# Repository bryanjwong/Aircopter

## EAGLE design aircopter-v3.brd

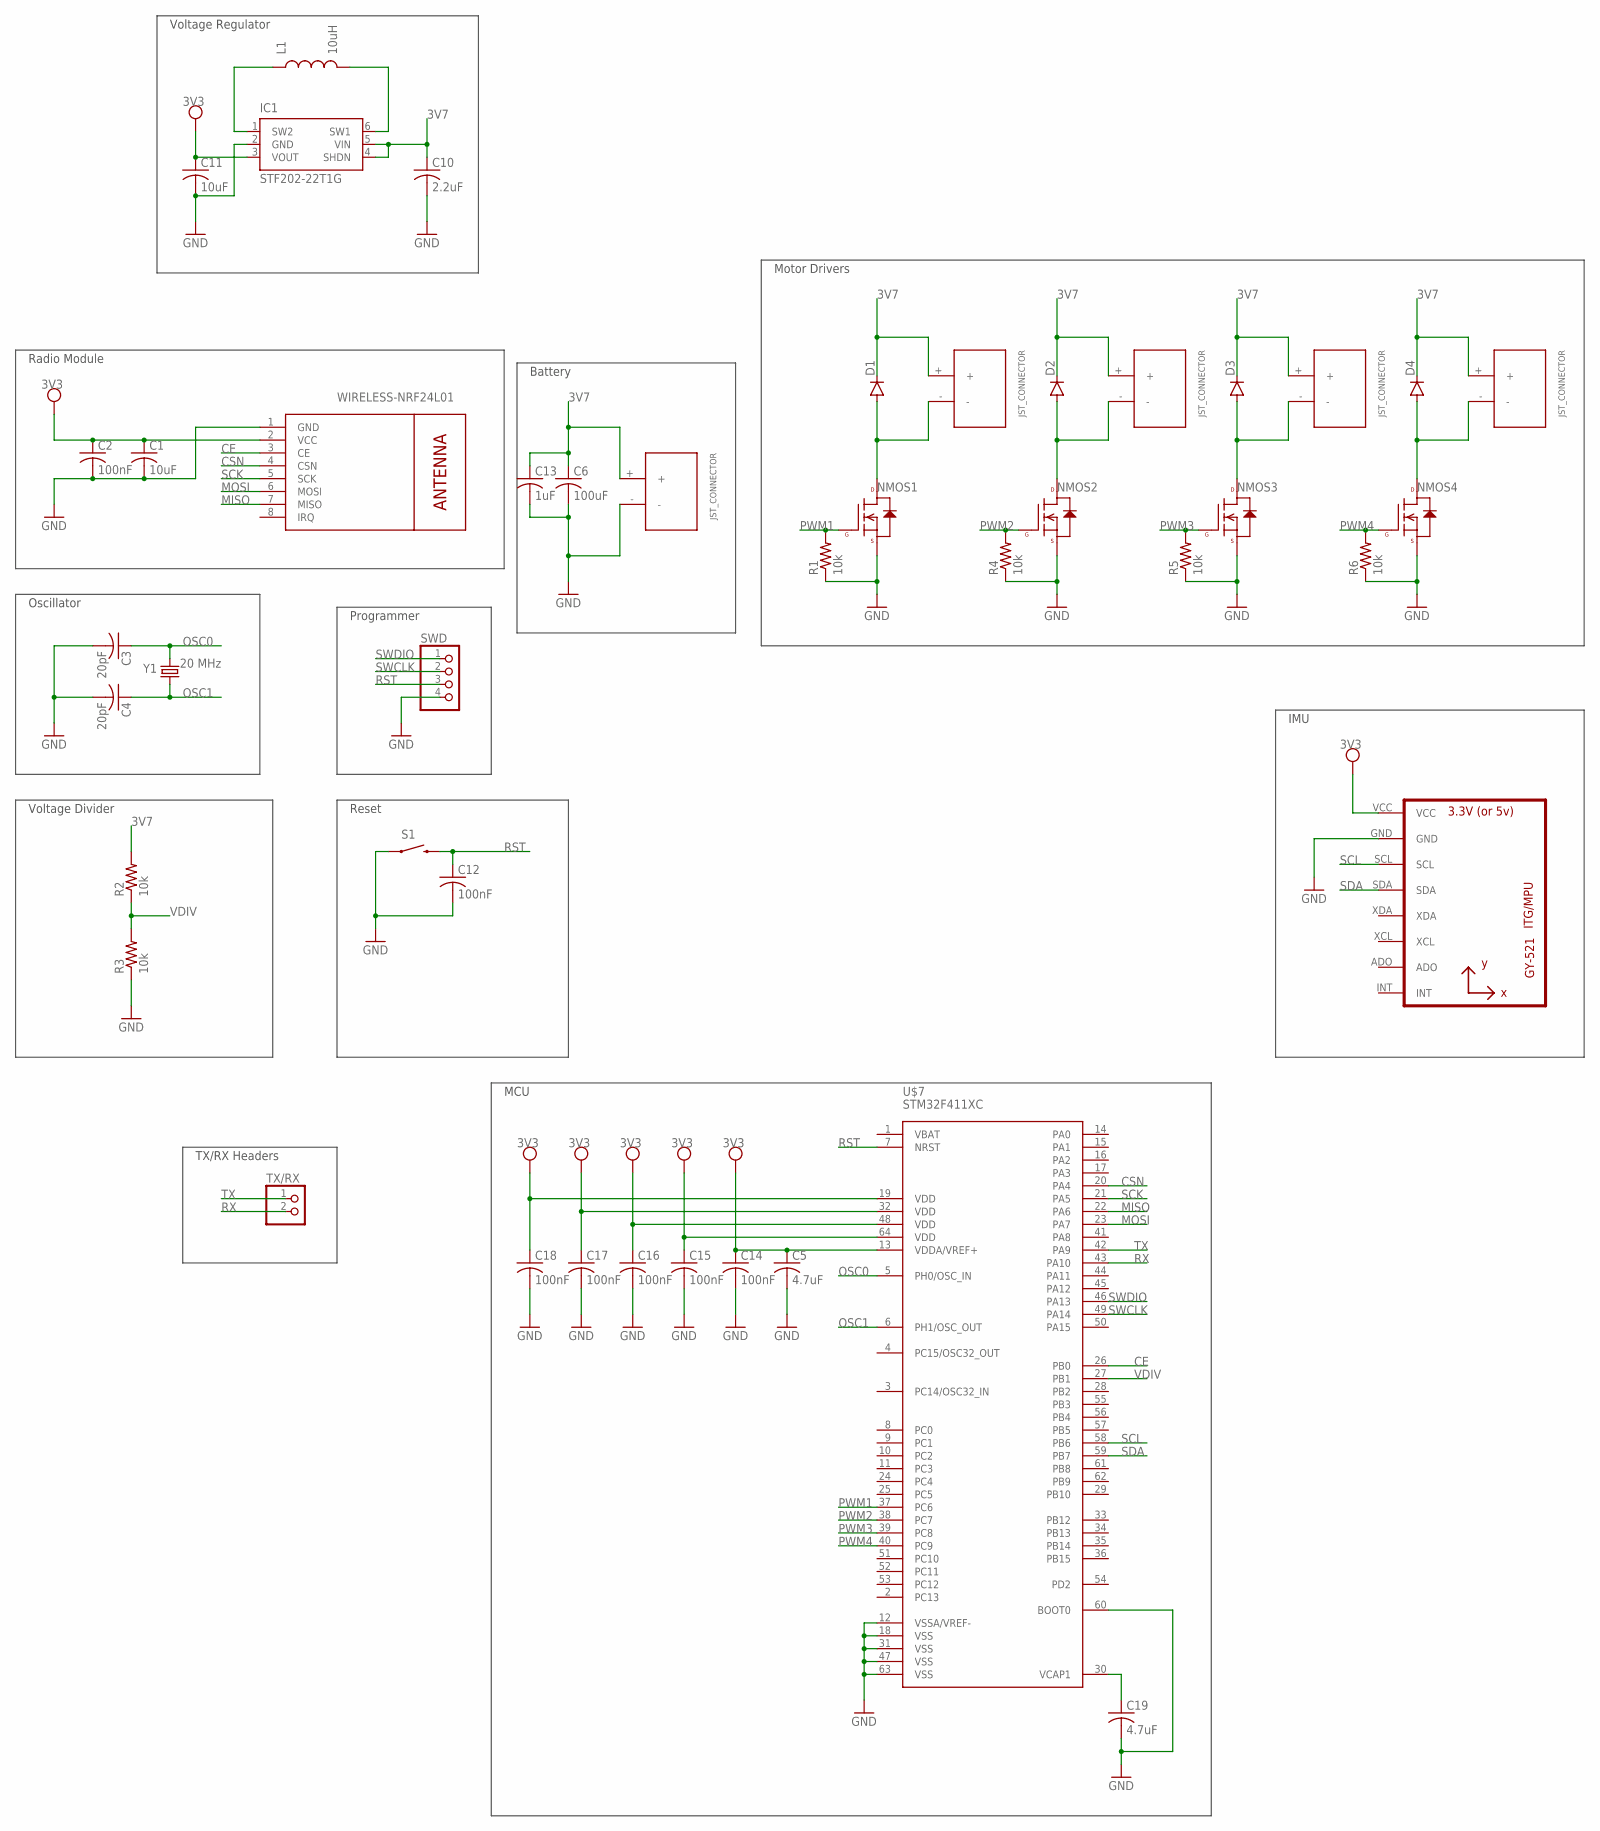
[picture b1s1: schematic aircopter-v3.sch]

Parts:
C1, C11: 10uF; C0603
C2, C12, C14, C15, C16, C17, C18: 100nF; C0603
C3, C4: 20pF; C0603
C5, C19: 4.7uF; C0603
C6: 100uF; C1206
C10: 2.2uF; C0603
C13: 1uF; C0603
D1, D2, D3, D4: DIODESMA; SMA-DIODE
IC1: STF202-22T1G; SOT23-6
L1: 10uH; L0603
M1: WIRELESS-NRF24L01
NMOS1, NMOS2, NMOS3, NMOS4: N-CHANNEL-MOSFET-BSS138; SOT23-3
R1, R2, R3, R4, R5, R6: 10k; R0603
S1: SWITCH-MOMENTARY-2SMD; TACTILE-SWITCH-SMD
SWD: PINHD-1X4; 1X04
TX/RX: PINHD-1X2; 1X02
U2: GY-521MPU6050; GY-521
U$2, U$3, U$4, U$5, U$6: JST_CONNECTOR_FEMALE
U$7: STM32F411XC; LQFP64
Y1: 20 MHz; HC49UP

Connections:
3V3: C1.1, C2.1, C5.1, C11.1, C14.1, C15.1, C16.1, C17.1, C18.1, IC1.3 (VOUT), M1.2 (VCC), U2.VCC, U$7.13 (VDDA/VREF+), U$7.19 (VDD), U$7.32 (VDD), U$7.48 (VDD), U$7.64 (VDD)
3V7: C6.1, C10.1, C13.1, D1.C, D2.C, D3.C, D4.C, IC1.4 (SHDN), IC1.5 (VIN), R2.2, U$2.+, U$3.+, U$4.+, U$5.+, U$6.+
CE: M1.3 (CE), U$7.26 (PB0)
CSN: M1.4 (CSN), U$7.20 (PA4)
GND: C1.2, C2.2, C3.2, C4.2, C5.2, C6.2, C10.2, C11.2, C12.2, C13.2, C14.2, C15.2, C16.2, C17.2, C18.2, C19.2, IC1.2 (GND), M1.1 (GND), NMOS1.2 (S), NMOS2.2 (S), NMOS3.2 (S), NMOS4.2 (S), R1.1, R3.1, R4.1, R5.1, R6.1, S1.1, SWD.4, U2.GND, U$6.-, U$7.12 (VSSA/VREF-), U$7.18 (VSS), U$7.31 (VSS), U$7.47 (VSS), U$7.60 (BOOT0), U$7.63 (VSS)
MISO: M1.7 (MISO), U$7.22 (PA6)
MOSI: M1.6 (MOSI), U$7.23 (PA7)
unnamed: D1.A, NMOS1.3 (D), U$2.-
unnamed: D2.A, NMOS2.3 (D), U$3.-
unnamed: D3.A, NMOS3.3 (D), U$4.-
unnamed: D4.A, NMOS4.3 (D), U$5.-
unnamed: IC1.1 (SW2), L1.1
unnamed: IC1.6 (SW1), L1.2
unnamed: C19.1, U$7.30 (VCAP1)
OSC0: C3.1, U$7.5 (PH0/OSC_IN), Y1.2
OSC1: C4.1, U$7.6 (PH1/OSC_OUT), Y1.1
PWM1: NMOS1.1 (G), R1.2, U$7.37 (PC6)
PWM2: NMOS2.1 (G), R4.2, U$7.38 (PC7)
PWM3: NMOS3.1 (G), R5.2, U$7.39 (PC8)
PWM4: NMOS4.1 (G), R6.2, U$7.40 (PC9)
RST: C12.1, S1.3 (2), SWD.3, U$7.7 (NRST)
RX: TX/RX.2, U$7.43 (PA10)
SCK: M1.5 (SCK), U$7.21 (PA5)
SCL: U2.SCL, U$7.58 (PB6)
SDA: U2.SDA, U$7.59 (PB7)
SWCLK: SWD.2, U$7.49 (PA14)
SWDIO: SWD.1, U$7.46 (PA13)
TX: TX/RX.1, U$7.42 (PA9)
VDIV: R2.1, R3.2, U$7.27 (PB1)

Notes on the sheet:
Motor Drivers
Programmer
IMU
Radio Module
Oscillator
Reset
Voltage Divider
Battery
Voltage Regulator
MCU
TX/RX Headers

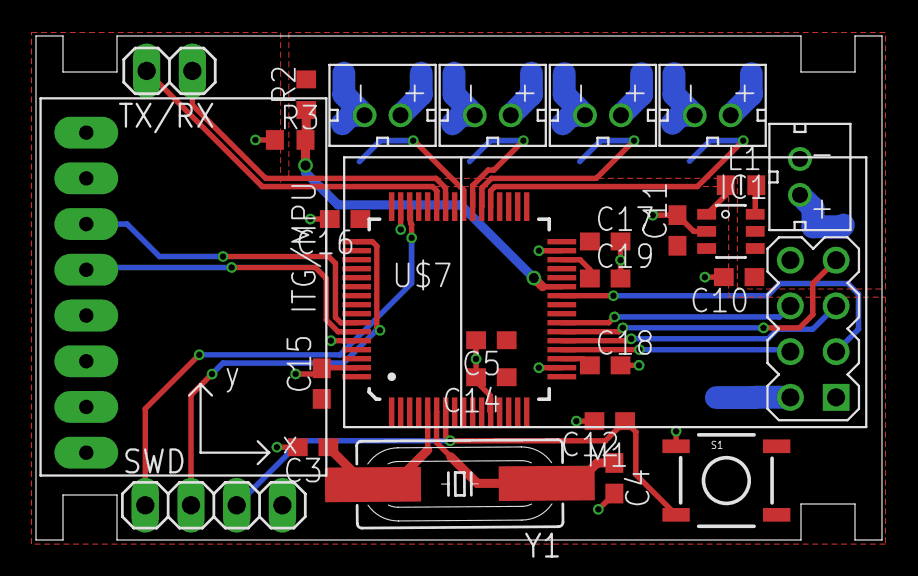
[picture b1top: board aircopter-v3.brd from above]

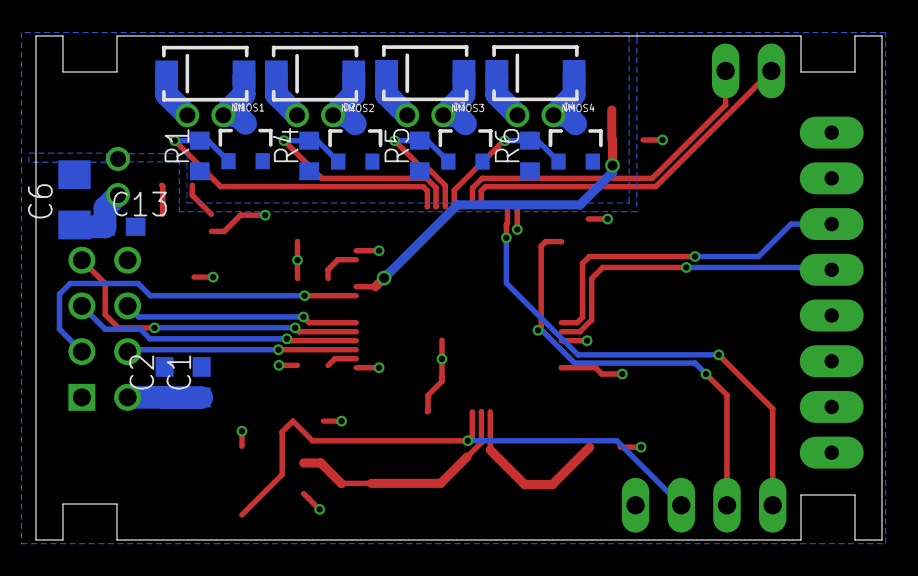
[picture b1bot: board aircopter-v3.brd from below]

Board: 2 copper layers, 47.0 x 28.0 mm, 44 parts (16 on the bottom side), 29 nets.

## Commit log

2020-01-31 added schematic
2020-01-31 added voltage regulator
2020-02-02 replaced mcu, minor fixes
2020-02-03 changed crystal load capacitance
2020-02-03 minor changes to mcu, added tx/rx headers
2020-02-03 minor fix to mcu
2020-02-03 minor mcu fixes again
2020-02-12 added libraries
2020-02-12 added another library
2020-02-12 another library
2020-02-12 worked on pcb
2020-02-12 removed backup files from repository
2020-02-12 Added Various Decoupling Caps
    Can someone check them b4 merge with master pls
2020-02-12 Fixed bugs, removed GND traces
2020-02-13 Added remaining caps, organized remaining components
    We're still missing the voltage regulator, voltage divider, and motor drivers,
2020-02-13 Bug Fixes
2020-02-13 Reorganized Remaining Comps, various bug fixes
2020-02-13 Moved libraries into separate folder
2020-02-13 pcb rough draft
2020-02-14 got rid of airwires
2020-02-17 added vias to avoid gnd bottlenecking
    made changes to 3V3, TX, and RX routes
2020-02-18 "Added vias to help with bottlenecking and resized the 3v7 plane"
2020-02-18 removed zip file
2020-02-20 Added Oshpark DRU, MGND and 3V3 planes
2020-02-26 moved battery and voltage reg, improved planes
2020-03-05 moved battery/voltage reg, moved motor comps, redid planes, minor fixes
2020-03-08 redid motor section and planes, slightly moved mcu and radio, other small changes
2020-03-08 filled in gnd plane through battery jst
